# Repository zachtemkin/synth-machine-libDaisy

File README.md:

# synthMachine

## Author

<!-- Insert Your Name Here -->

## Description

<!-- Describe your example here -->

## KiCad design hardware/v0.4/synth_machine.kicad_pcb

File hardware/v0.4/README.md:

# synthMachine carrier board v0.4

Second revision of the carrier. v0.3 in `../v0.3/` is the board that was
fabricated in September 2026; v0.4 applies everything in `../NEXT_REVISION.md`
and adds onboard battery power. It is a new outline: 160 x 74 mm landscape
instead of 100 x 100, with all 19 key headers in one row along the bottom
edge in panel order. The USB-C, the Seed's own USB and the headphone jack
still share the top edge.

| Change | Parts | Why |
|---|---|---|
| One row of key headers | K1..K19 along the bottom at 7 mm pitch, diode above each, name below | Every button lead is the same length and points the same way. The headers are rotated so the row is 132 mm wide and the corners stay free for mounting holes. |
| Battery power | J17 JST-PH cell, U5 BQ24074 charger with power path, U6 TPS61023 5 V boost, J16 power-switch header, JP2 always-on jumper | Runs from a single LiPo, charges from the USB-C, and runs from USB while charging. See the power section below. |
| Plug detect reaches 3V3 | Q1 is a 2N7002 MOSFET | The v0.3 BJT clamped HP_DET at 0.8 V so D13 never saw a plug. No jumper, no `HP_DET=adc`. |
| Firmware mute on its own transistor | Q2 2N7002, R6 gate, R15 pull-up; MUTE on D0 | Muted at reset, in DFU and after a crash; firmware drives D0 low to run. Wired-OR with Q1. |
| I2C for encoders | J15 STEMMA QT (top-entry) on I2C1 (D11 SCL, D12 SDA) at the top right; R16/R17 pull-ups DNP | For the seesaw rotary-encoder breakouts; the cable leaves upward toward the panel. |
| Display header | J9: GND, 3V3, 5V, SCK (A7), MOSI (A3), NSS (A8), D/C (D26), RST (D27) | Hardware SPI1 for an OLED or a Sharp memory LCD. |
| Encoders instead of bank pots | J11..J14 removed; only J10 (volume) remains | The four bank controls are seesaw rotary encoders on J15. Their old ADC pins go to the expansion header. |
| USB ESD, SMD fuse | U4 USBLC6-2SC6, F1 1812 PTC on the USB input | Data lines were unprotected; the radial fuse collided with the Seed. |
| USB-C receptacle | J1 is the HRO TYPE-C-31-M-12 (LCSC C165948) | Same land pattern and body depth as v0.3's GCT USB4105, which went out of stock. A JLCPCB basic part. |
| Peripheral 3.3 V rail | U7 AP7361C-33 (SOT-223, 1 A) from +5V, C27/C28 | Feeds the encoders, the display and the expansion header's 3V3 pin, so the Seed's regulator carries only the Seed, the headphone amp and pull-ups. |
| Assembly-ready BOM | every part has an MPN or LCSC number | `fab.sh` writes `pcbway_bom.csv` / `pcbway_cpl.csv`. |

Only the volume pot header remains (A0). The four bank controls are I2C
rotary encoders on J15, chained over STEMMA QT. The firmware profile
`HW=carrier4` reads A0 only and leaves the bank inputs alone until the
encoder support exists.

## Power

```
USB-C J1 -> F1 2.5 A PTC -> VUSB -> U5 BQ24074 IN
                                    U5 BAT  <-> J17 cell (+ C22)
                                    U5 OUT   -> VSYS (4.4 V on USB, else the cell)
VSYS -> L1 1 uH / U6 TPS61023 -> +5V (5.1 V) -> Seed VIN, speaker amp, J8/J9 5V pins
                                       +5V -> U7 AP7361C-33 -> 3V3P -> J15 encoders, J9 display, J8 3V3
```

- **Charger.** EN2 high and EN1 low select the resistor-programmed input
  limit: R19 1.1k gives 1.5 A, and the charger's input-voltage loop backs off
  automatically on a weak USB port. R18 1.8k sets 0.5 A fast charge, which is
  0.25 C for a 2000 mAh cell and keeps the linear charger under 0.7 W. TMR and
  ITERM are left open for the default 30 min / 5 h safety timers and 10 %
  termination. CE is tied low, TS has the 10k that the part needs when there
  is no pack thermistor. The system runs from OUT while the cell charges, and
  the cell supplements USB on peaks.
- **Boost.** The TPS61023 makes 5.1 V from VSYS (750k/100k on a 0.6 V
  reference). It carries the whole load on USB as well as on battery, which is
  fine: from the charger's 4.4 V it is barely working. From a 3.3 V cell it
  delivers about 1.5 A continuous with the 470 uF C1 covering the amp's
  peaks. Inductor per TI's table (Coilcraft XEL4030-102ME); XGL4030-102MEC is
  the LCSC-stocked equivalent.
- **Switch.** J16 takes a panel SPST. Closed, it pulls the boost's EN up to
  VSYS through R28; open, R27 holds it low and everything downstream of the
  boost is off, while the charger keeps charging. The EN pin draws nothing,
  so any small switch works. J16 sits on the left edge at mid-height with JP2
  beside it to bridge the switch on a bench board; the two enable lines run
  across the board to the boost, which is fine for a pull-up-and-pin signal.
- **Firmware signals.** A10 reads VBAT/2 (R23/R24, 0 to 2.1 V). A5 reads
  ~CHG (low = charging) and A11 reads ~PGOOD (low = USB present), both
  open-drain with 100k pull-ups. Nothing in the firmware uses them yet.
- **Cell.** Single-cell LiPo on J17, pin 1 = +. Use a protected cell (the
  Adafruit and SparkFun packs are); there is no protection on the board.
  2000 mAh or more suits the speakers, which can pull over 1 A at volume.
- **Note.** The Seed's own USB port powers only the Seed; it cannot charge
  the cell or run the amp. That was already true on v0.3.

## Regenerate, route, fab

Same pipeline as v0.3, run from this directory:

```bash
KICAD_PY=/Applications/KiCad/KiCad.app/Contents/Frameworks/Python.framework/Versions/Current/bin/python3
$KICAD_PY hardware/v0.4/gen_kicad.py                       # schematic + placed PCB
$KICAD_PY hardware/v0.4/route.py --java <java25> --jar freerouting-2.4.1.jar
$KICAD_PY hardware/v0.4/route.py --pours-only              # rebuild just the GND pours
sh hardware/v0.4/fab.sh                                    # Gerbers, BOMs, CPLs, test print
```

Freerouting 2.4.1 needs Java 25. Neither is installed system-wide on the
Mac; a portable Temurin JRE from adoptium.net and the jar from the Freerouting
GitHub releases page were used, and both can live anywhere. `PREROUTES` in
the generator carries the audio paths, the MAX98306 fan-out and short stubs
off the boost converter's 0.5 mm pitch pins, which the autorouter cannot reach
with power-width tracks on its own.

## Pin map (what the firmware profile `HW=carrier4` expects)

| Seed pin | Use |
|---|---|
| D0 | MUTE: high = speakers muted (default via R15), low = run |
| D1..D3 | matrix rows |
| D4..D9 | matrix columns |
| D10 | C4 key |
| D11, D12 | I2C1 SCL, SDA (STEMMA QT) |
| D13 | HP_DET, high = headphones plugged in |
| D14 | HP_MUTE, headphone amp ~MUTE, low = muted |
| A0 | volume pot |
| A1, A2, A4, A9 | spare, on J8 (the old bank pot inputs) |
| A3, A7, A8 | SPI1 MOSI, SCK, NSS (display) |
| A5 | ~CHG from the charger, low = charging |
| A6 | spare, on J8 (seesaw INT candidate) |
| A10 | battery voltage / 2 |
| A11 | ~PGOOD from the charger, low = USB present |
| D26, D27 | display D/C, RST |
| D29, D30 | USB-C data (MIDI) |

## Headers

| Ref | What | Pins |
|---|---|---|
| K1..K19 | keys, JST-XH 2-pin, bottom row in panel order | row / diode (any way round) |
| J10 | volume pot, JST-XH 3-pin, left edge below the USB-C | 3V3A, wiper, GND |
| J5, J6 | speakers, JST-PH | + / - |
| J17 | battery, JST-PH | 1 = +, 2 = GND |
| J16 | power switch, JST-XH 2-pin, left edge mid-height (JP2 beside it bridges it) | either way round |
| J15 | STEMMA QT, top-entry, top right | GND, 3V3P, SDA, SCL |
| J9 | display | GND, 3V3P, 5V, SCK, MOSI, NSS, D/C, RST |
| J8 | expansion | HP_MUTE, A1, A2, A4, A6, A9, HP_DET, MUTE, VSYS, 3V3P, 5V, GND |

## Ordering with assembly (PCBWay)

`fab.sh` writes `fab/pcbway_bom.csv` with an item per line: designators,
quantity, manufacturer part number, LCSC number, value, package and whether it
is SMD or through-hole. `fab/pcbway_cpl.csv` has both sides. Upload the
Gerber zip, the BOM and the CPL; on the quote, tick at least J1 (USB-C), the
19 K headers, J10, J5/J6, J16, J17 and J15 for placement. The Seed
sockets, C1 and the jack can go in the same job or be hand-fitted.

## Ordering with assembly (JLCPCB)

`fab/jlcpcb_bom.csv` and `fab/jlcpcb_cpl.csv` carry every part with an LCSC
number, which is all of the SMD parts and the JST connectors: the 19 key
headers, the volume and switch headers (JST XH originals, C158012 /
C144394) and the speaker and battery sockets (JST PH, C131337). Choose
**standard** assembly, not economic: economic is SMD-only and drops the
through-hole connectors. Still hand-fitted afterwards: the two Seed sockets,
the two expansion/display sockets, the headphone jack and C1, which are on
the Digi-Key list. The DNP pull-ups are excluded automatically.

## Design review notes (v0.4 quality pass)

Things checked after the layout settled, and what was changed or accepted:

- **Current paths.** Every net that carries real current was audited for
  width: VBUS/VUSB/VBAT/VSYS 0.4 mm, +5V and the filtered speaker lines
  0.6 mm, with 0.5 mm-drill vias. The only narrow copper left is the
  unavoidable necks onto fine-pitch pads: 0.3 mm for less than 1 mm at the
  boost's VIN/SW/VOUT/GND pins (0.35 mm pads, 0.5 mm pitch) and 0.2 mm for
  about 1 mm at the amp's PVDD and speaker pins (0.4 mm pitch). The amp's
  two PVDD pins are joined right off the pads into one 0.5 mm feed. The
  boost's input and output capacitors sit at its pins with 0.6 mm copper.
- **Power switch really switches off.** The TPS61023 has true input-to-output
  disconnect in shutdown, so with EN low nothing reaches the Seed's VIN.
- **Bulk capacitor on the boost.** The 470 uF electrolytic on +5V is inside
  the TPS61023's stated 4 to 1000 uF effective output range.
- **Boost thermals.** SOT-563 is about 120 to 140 K/W. At 1 A out from a
  3.3 V cell the part dissipates about 0.5 W, so it runs warm (60 K rise)
  but within limits; the amp's 2 A peaks are brief. Keep the ground pour
  under it. If a future revision needs more headroom, the TPS61088 in a
  QFN is the drop-in class.
- **Seed 3V3 budget.** Solved with a separate rail: the Seed's regulator
  feeds only the Seed, the headphone amp and the pull-ups (tens of
  milliamps). The encoders, display and expansion header run from U7, a
  1 A SOT-223 LDO on the +5V rail (3V3P). At 300 mA it dissipates about
  0.55 W, a 30 K rise on its ground tab and pour. On battery that rail is
  boost-then-LDO, roughly 60 % efficient, about 20 mA of extra cell current
  at typical loads. The headphone amp stays on the Seed's quieter rail.
- **USB-C current.** The CC pull-downs advertise a sink but the firmware does
  not read the source's advertisement, so the charger's 1.5 A input limit
  applies to any port; the charger's VIN-DPM loop throttles rather than
  crashes a 500 mA port. A CC ADC read would let firmware lower ILIM later.
- **Battery divider on the ADC.** 100k/100k is a 50k source impedance, high
  for the STM32 ADC's sampling time; the 100 nF across the bottom resistor
  is what makes the reading settle. Do not drop it.
- **Reverse cell.** No reverse-polarity protection on J17 by design (a diode
  would cost the charger its regulation). The polarity check below is the
  protection.
- **Quiescent when off.** Charger from the cell, boost leakage and the sense
  divider add up to about 25 uA, years on any usable cell.

## Check before ordering

1. **J17 polarity** against the cell you will use: pin 1 is + here, and the
   silkscreen says so. A reversed cell destroys the charger.
2. **J15 pin 1** (GND) is the pad nearest the board's right edge; check it
   against the cable's black wire before plugging in an encoder board.
3. **Q1/Q2 pinout:** KiCad's `Q_NMOS_GSD` is gate 1, source 2, drain 3, the
   2N7002's SOT-23 order. Check the LCSC part's datasheet agrees.
4. **U5 thermal pad** has vias to the ground pour; make sure the assembler's
   stencil does not flood it.
5. **Enclosure:** the outline changed. The top edge still carries all three
   ports at the same spacing from the left edge as v0.3, but the board is
   60 mm wider and 26 mm shorter, and the mounting holes moved. The headphone
   jack's nose now stands 1.5 mm proud of the edge instead of flush.
6. **F1 and L1 look unpopulated in the render** only because this KiCad
   install has no 3D models for the 1812 fuse and the XxL4030 inductor
   footprints. Both are in the BOM and the placement file.

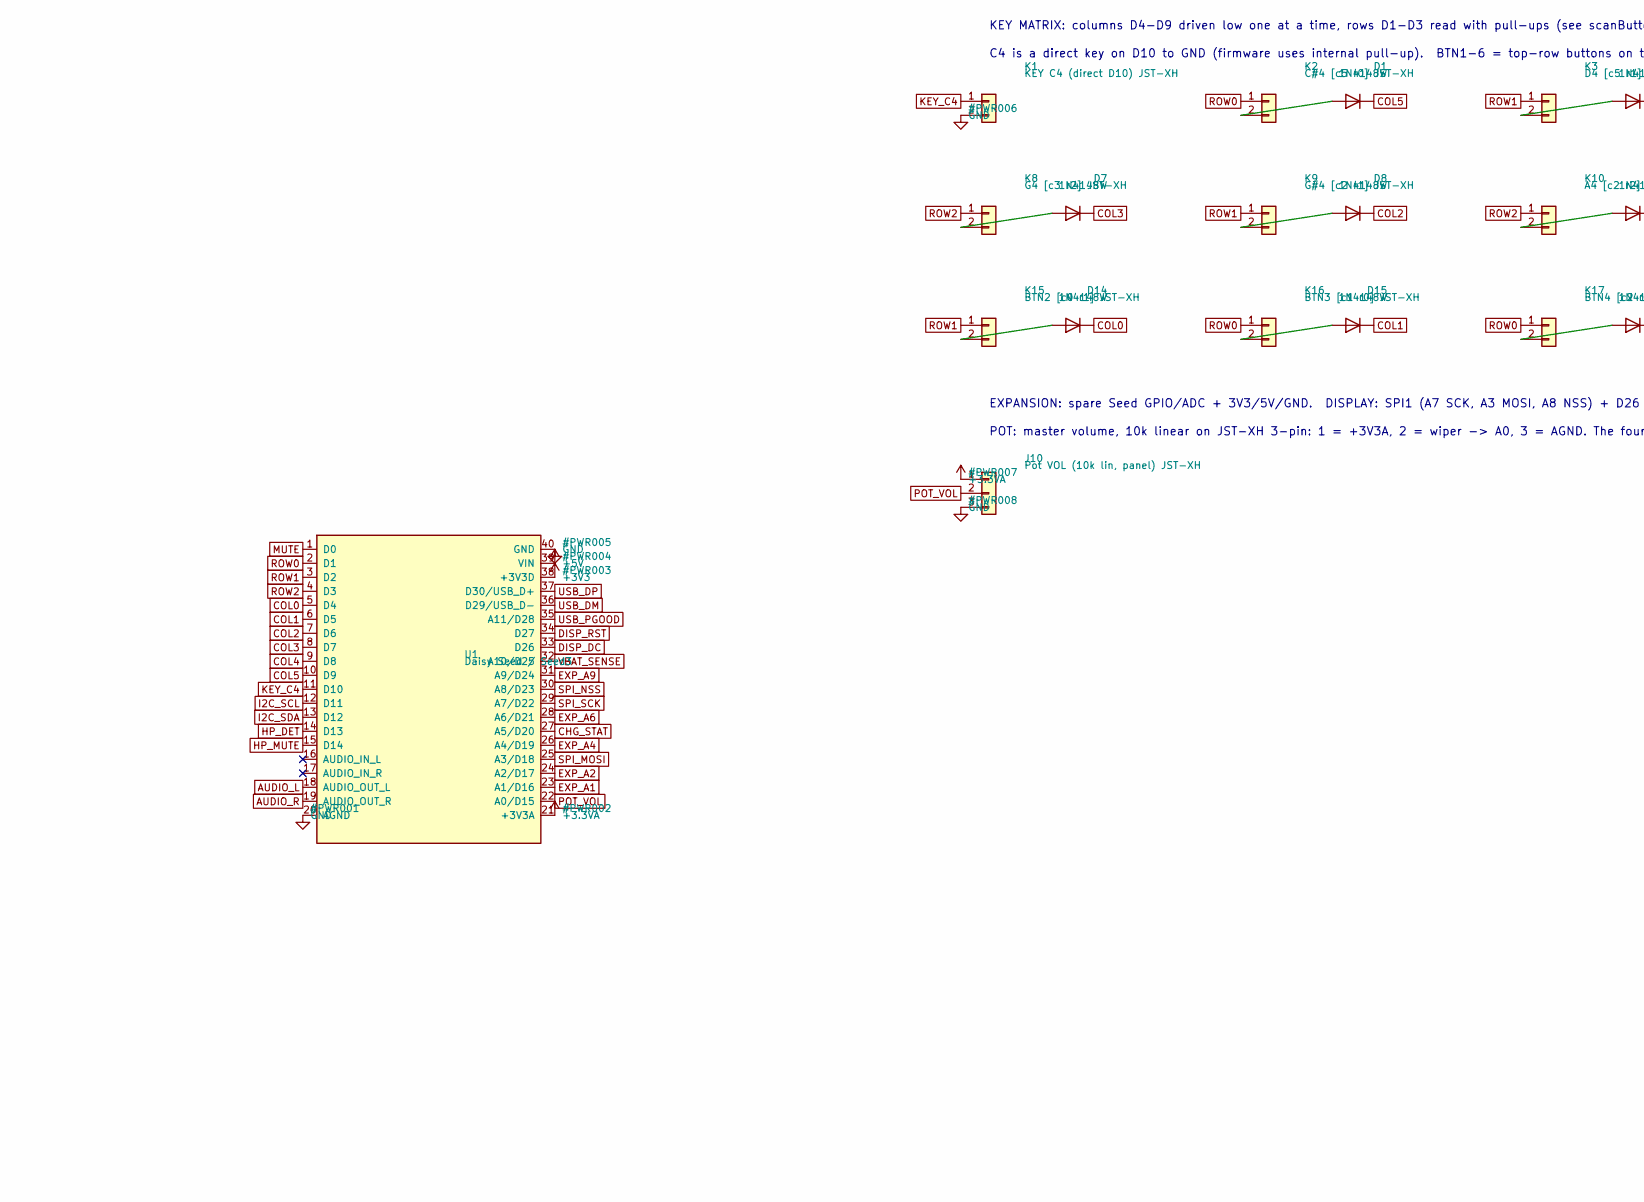
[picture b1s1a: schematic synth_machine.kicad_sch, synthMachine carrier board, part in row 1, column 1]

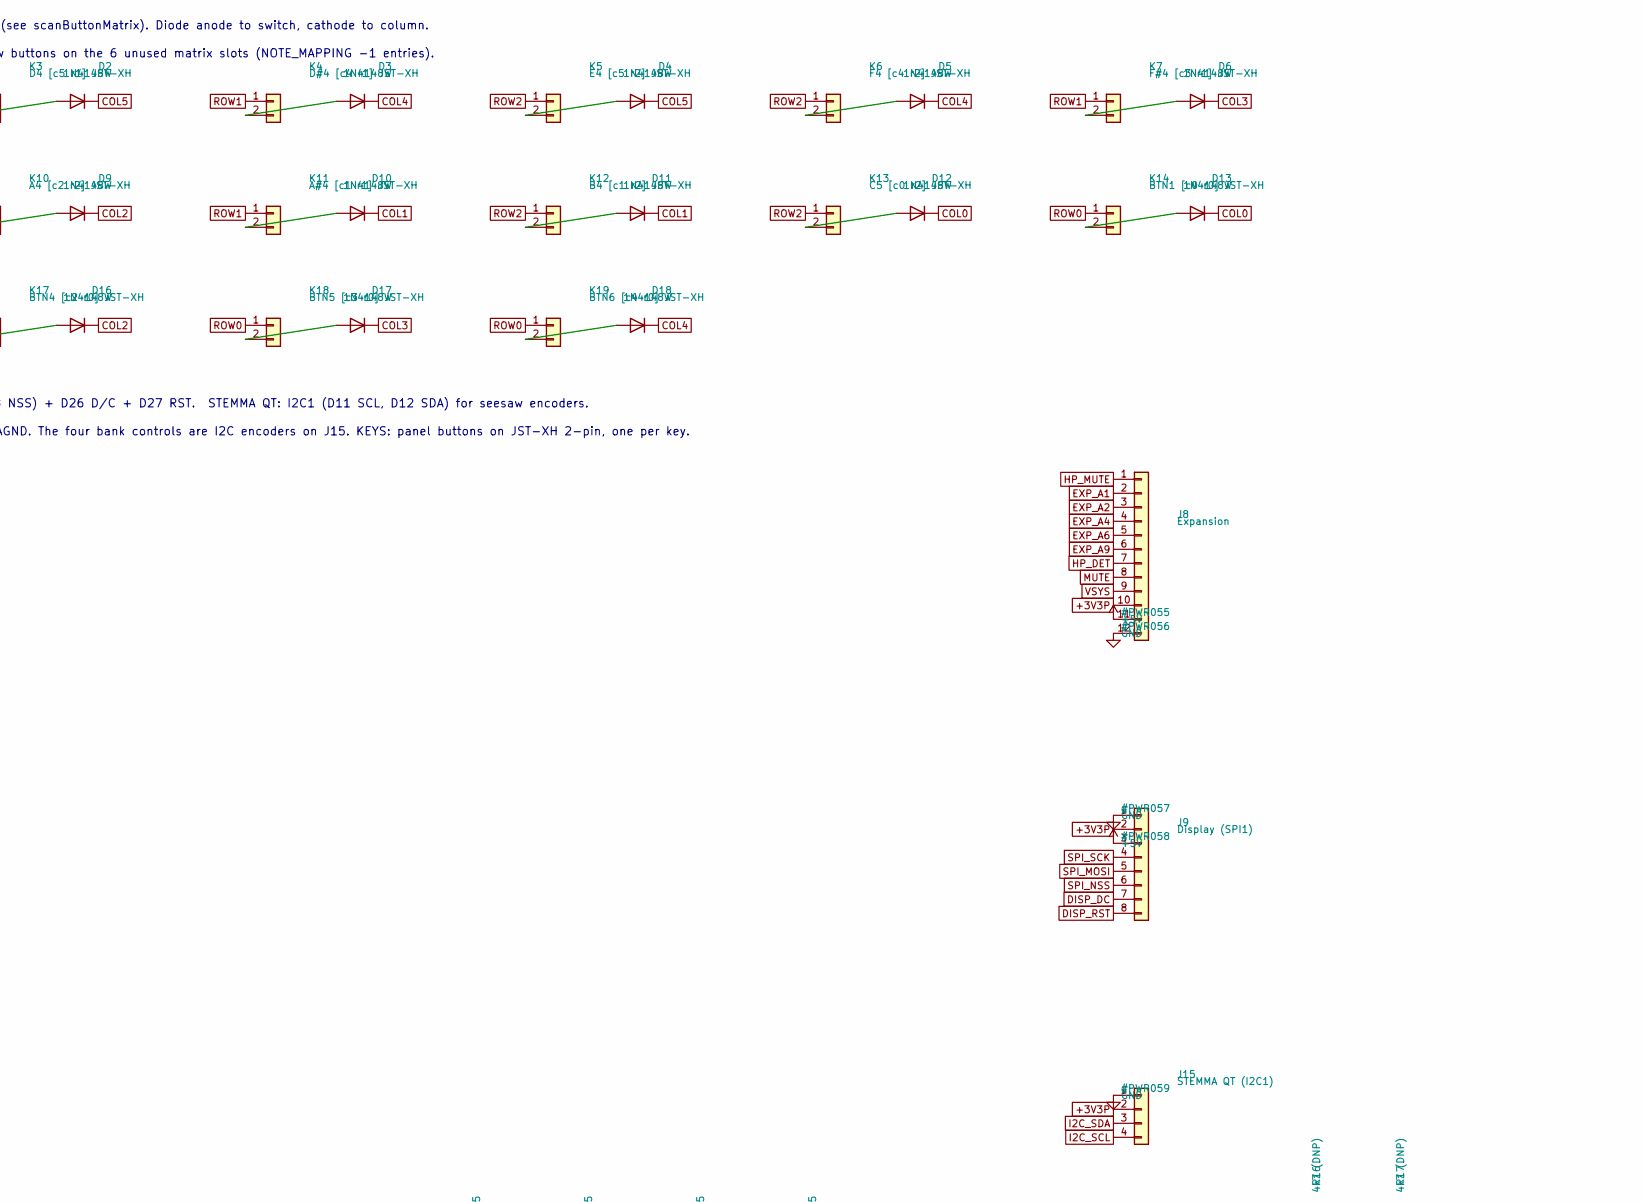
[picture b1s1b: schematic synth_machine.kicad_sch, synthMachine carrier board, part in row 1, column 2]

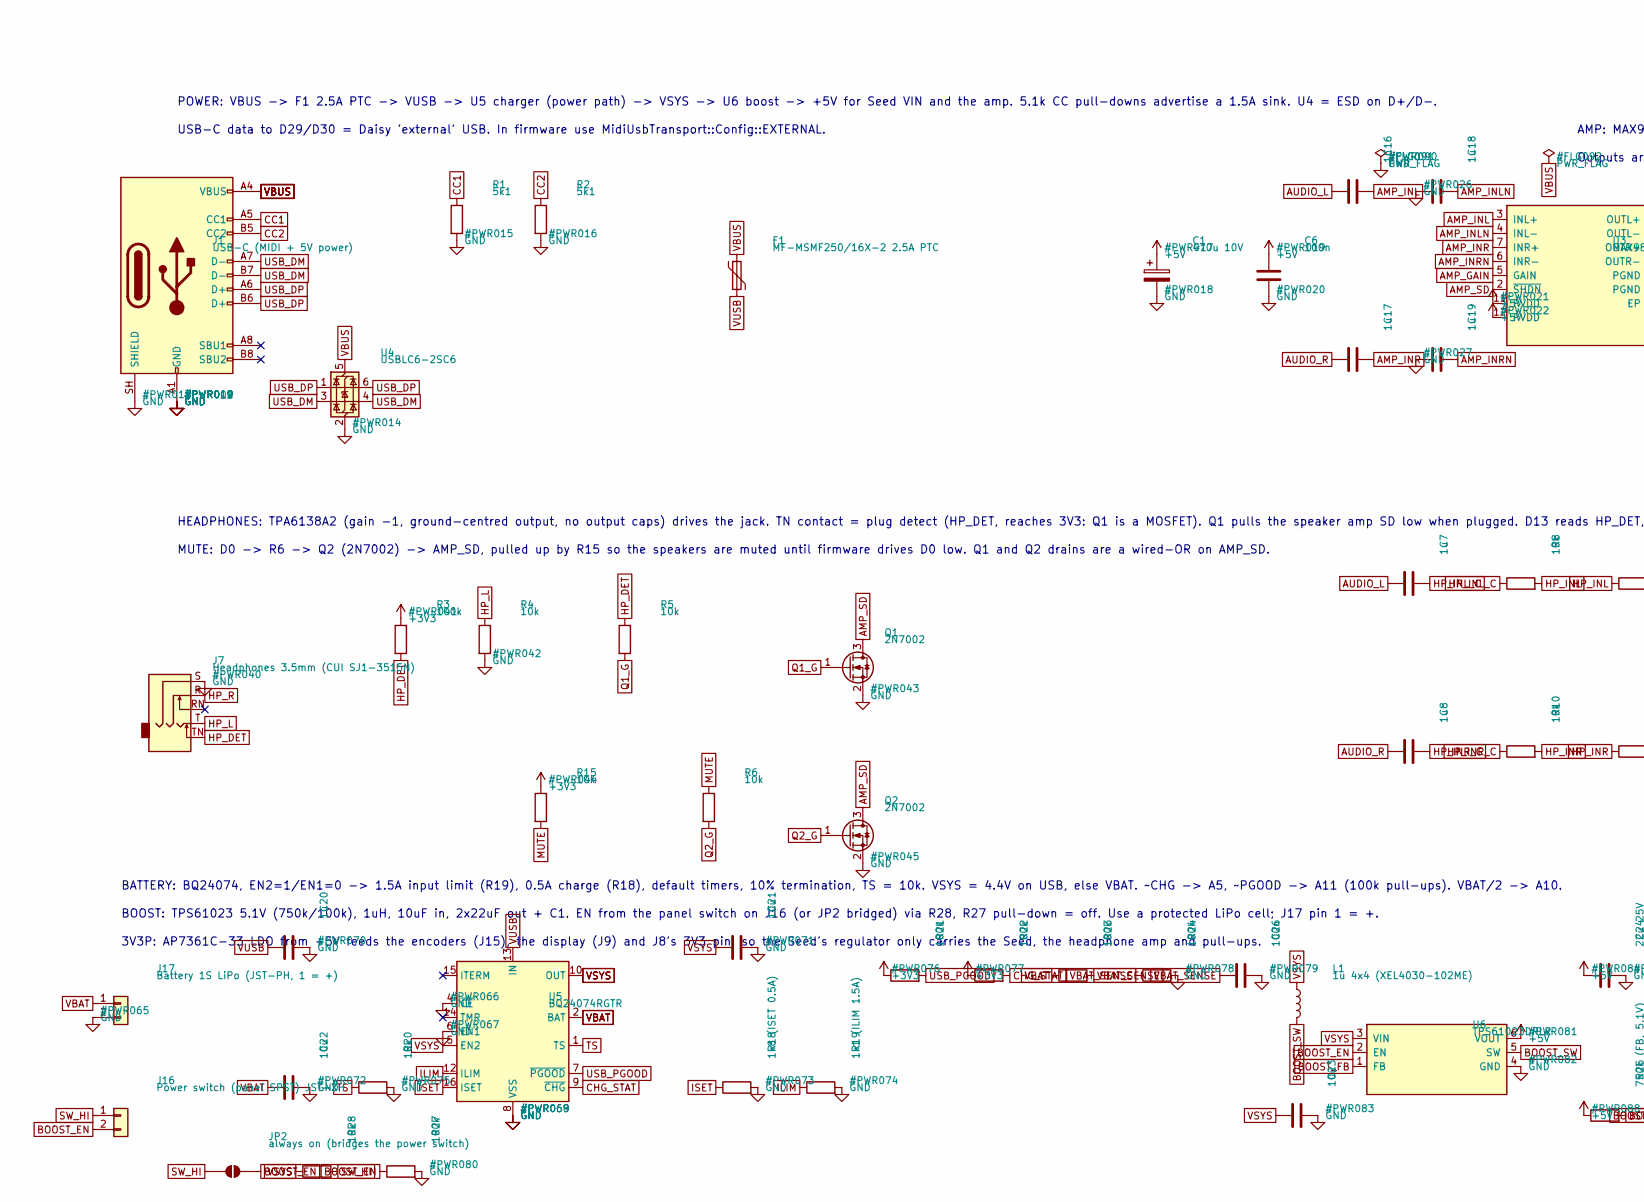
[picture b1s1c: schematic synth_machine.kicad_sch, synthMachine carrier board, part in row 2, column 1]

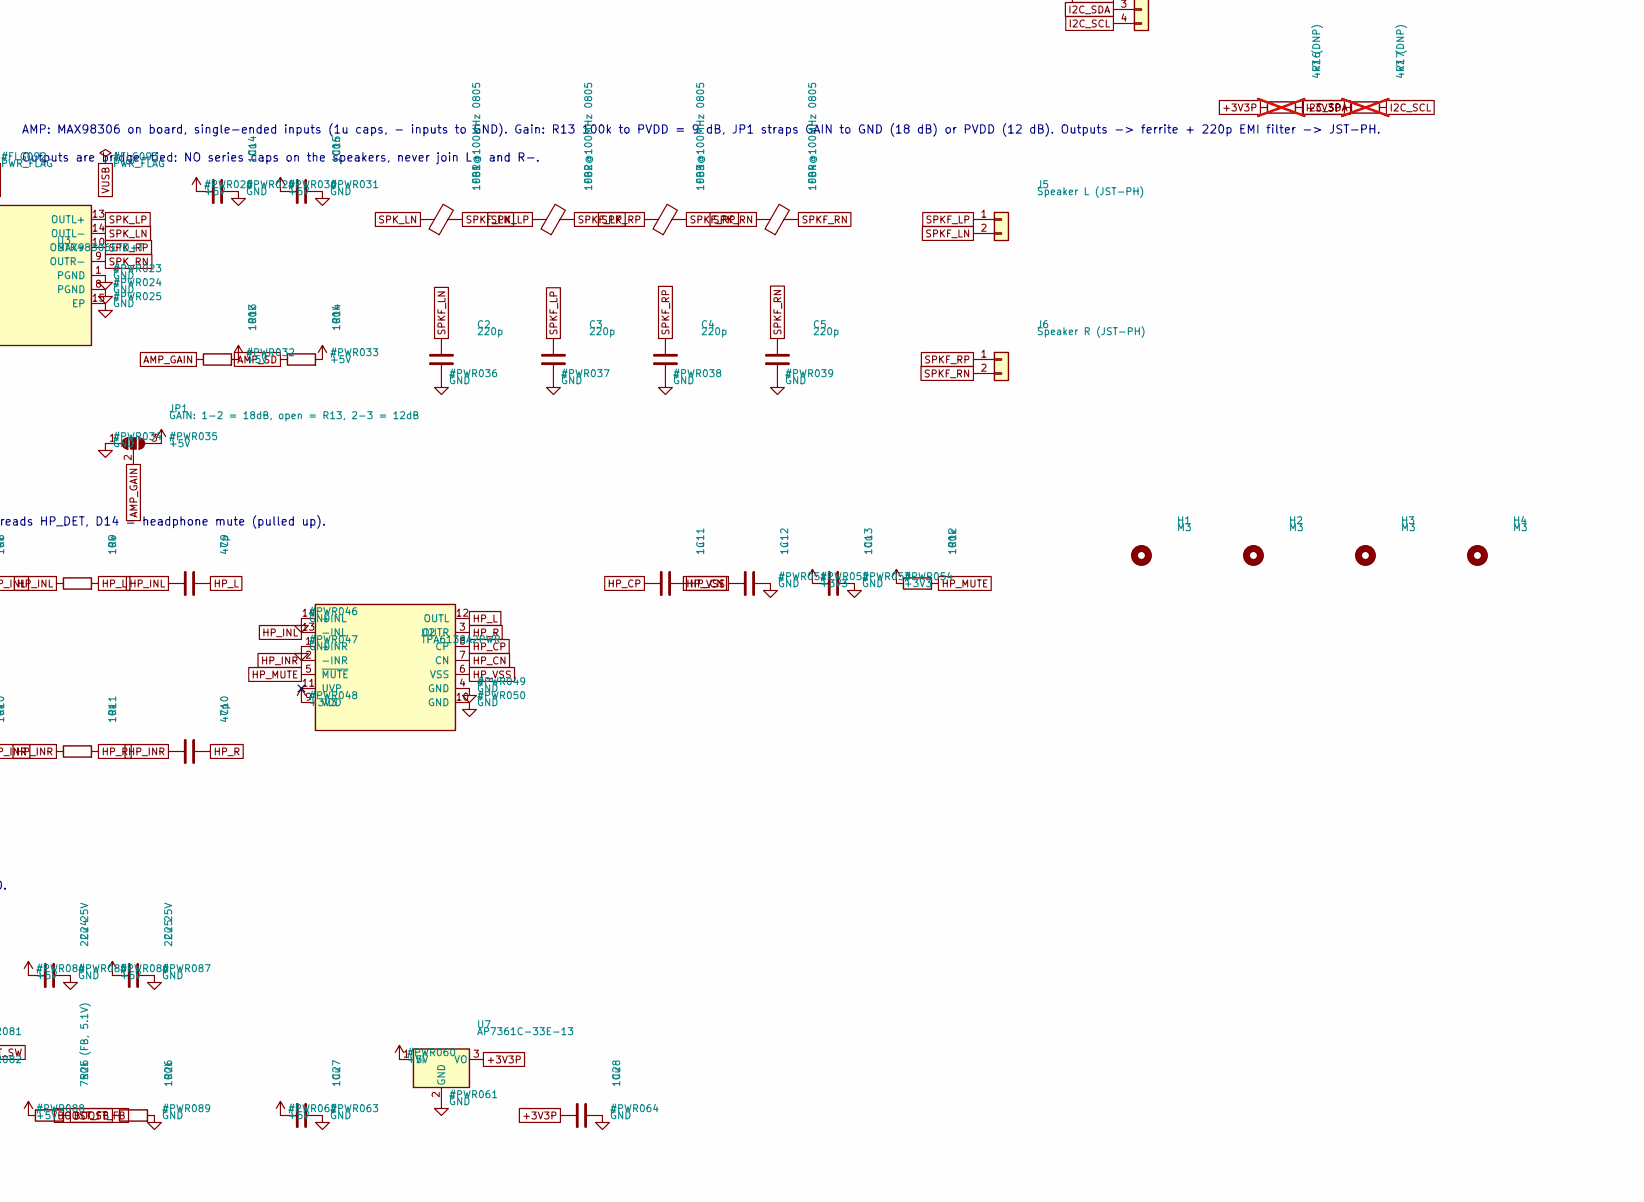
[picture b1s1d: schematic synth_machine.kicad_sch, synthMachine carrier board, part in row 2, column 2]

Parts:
C1: 470u 10V; CP_Radial_D8.0mm_P3.50mm; MPN EEU-FR1A471
C2, C3, C4, C5: 220p; C_0805_2012Metric; LCSC C53172
C6, C15, C26: 100n; C_0805_2012Metric; LCSC C49678
C7, C8, C11, C12, C16, C17, C18, C19, C20: 1u; C_0805_2012Metric; LCSC C28323
C9, C10: 47p; C_0805_2012Metric; LCSC C14857
C13, C14, C21, C22, C23, C27, C28: 10u; C_0805_2012Metric; LCSC C15850
C24, C25: 22u 25V; C_1210_3225Metric; MPN CL32A226KAJNNNE; LCSC C52306
D1, D2, D3, D4, D5, D6, D7, D8, D9, D10, D11, D12, D13, D14, D15, D16, D17, D18: 1N4148W; D_SOD-123; LCSC C81598
F1: MF-MSMF250/16X-2 2.5A PTC; Fuse_1812_4532Metric; MPN MF-MSMF250/16X-2; LCSC C210838
FB1, FB2, FB3, FB4: 100R@100MHz 0805; L_0805_2012Metric; LCSC C1015
H1, H2, H3, H4: M3; MountingHole_3.2mm_M3
J1: USB-C (MIDI + 5V power); USB_C_Receptacle_HRO_TYPE-C-31-M-12; MPN TYPE-C-31-M-12; LCSC C165948
J5: Speaker L (JST-PH); JST_PH_B2B-PH-K_1x02_P2.00mm_Vertical; MPN B2B-PH-K-S(LF)(SN); LCSC C131337
J6: Speaker R (JST-PH); JST_PH_B2B-PH-K_1x02_P2.00mm_Vertical; MPN B2B-PH-K-S(LF)(SN); LCSC C131337
J7: Headphones 3.5mm (CUI SJ1-3515N); Jack_3.5mm_CUI_SJ1-3515N_Horizontal; MPN SJ1-3515N
J8: Expansion; PinHeader_1x12_P2.54mm_Vertical; MPN PPTC121LFBN-RC
J9: Display (SPI1); PinHeader_1x08_P2.54mm_Vertical; MPN PPTC081LFBN-RC
J10: Pot VOL (10k lin, panel) JST-XH; JST_XH_B3B-XH-A_1x03_P2.50mm_Vertical; MPN B3B-XH-A(LF)(SN); LCSC C144394
J15: STEMMA QT (I2C1); JST_SH_BM04B-SRSS-TB_1x04-1MP_P1.00mm_Vertical; MPN BM04B-SRSS-TB(LF)(SN); LCSC C160390
J16: Power switch (panel SPST) JST-XH; JST_XH_B2B-XH-A_1x02_P2.50mm_Vertical; MPN B2B-XH-A(LF)(SN); LCSC C158012
J17: Battery 1S LiPo (JST-PH, 1 = +); JST_PH_B2B-PH-K_1x02_P2.00mm_Vertical; MPN B2B-PH-K-S(LF)(SN); LCSC C131337
JP1: GAIN: 1-2 = 18dB, open = R13, 2-3 = 12dB; SolderJumper-3_P1.3mm_Open_RoundedPad1.0x1.5mm
JP2: always on (bridges the power switch); SolderJumper-2_P1.3mm_Open_RoundedPad1.0x1.5mm
K1: KEY C4 (direct D10) JST-XH; JST_XH_B2B-XH-A_1x02_P2.50mm_Vertical; MPN B2B-XH-A(LF)(SN); LCSC C158012
K2: C#4 [c5 r0] JST-XH; JST_XH_B2B-XH-A_1x02_P2.50mm_Vertical; MPN B2B-XH-A(LF)(SN); LCSC C158012
K3: D4 [c5 r1] JST-XH; JST_XH_B2B-XH-A_1x02_P2.50mm_Vertical; MPN B2B-XH-A(LF)(SN); LCSC C158012
K4: D#4 [c4 r1] JST-XH; JST_XH_B2B-XH-A_1x02_P2.50mm_Vertical; MPN B2B-XH-A(LF)(SN); LCSC C158012
K5: E4 [c5 r2] JST-XH; JST_XH_B2B-XH-A_1x02_P2.50mm_Vertical; MPN B2B-XH-A(LF)(SN); LCSC C158012
K6: F4 [c4 r2] JST-XH; JST_XH_B2B-XH-A_1x02_P2.50mm_Vertical; MPN B2B-XH-A(LF)(SN); LCSC C158012
K7: F#4 [c3 r1] JST-XH; JST_XH_B2B-XH-A_1x02_P2.50mm_Vertical; MPN B2B-XH-A(LF)(SN); LCSC C158012
K8: G4 [c3 r2] JST-XH; JST_XH_B2B-XH-A_1x02_P2.50mm_Vertical; MPN B2B-XH-A(LF)(SN); LCSC C158012
K9: G#4 [c2 r1] JST-XH; JST_XH_B2B-XH-A_1x02_P2.50mm_Vertical; MPN B2B-XH-A(LF)(SN); LCSC C158012
K10: A4 [c2 r2] JST-XH; JST_XH_B2B-XH-A_1x02_P2.50mm_Vertical; MPN B2B-XH-A(LF)(SN); LCSC C158012
K11: A#4 [c1 r1] JST-XH; JST_XH_B2B-XH-A_1x02_P2.50mm_Vertical; MPN B2B-XH-A(LF)(SN); LCSC C158012
K12: B4 [c1 r2] JST-XH; JST_XH_B2B-XH-A_1x02_P2.50mm_Vertical; MPN B2B-XH-A(LF)(SN); LCSC C158012
K13: C5 [c0 r2] JST-XH; JST_XH_B2B-XH-A_1x02_P2.50mm_Vertical; MPN B2B-XH-A(LF)(SN); LCSC C158012
K14: BTN1 [c0 r0] JST-XH; JST_XH_B2B-XH-A_1x02_P2.50mm_Vertical; MPN B2B-XH-A(LF)(SN); LCSC C158012
K15: BTN2 [c0 r1] JST-XH; JST_XH_B2B-XH-A_1x02_P2.50mm_Vertical; MPN B2B-XH-A(LF)(SN); LCSC C158012
K16: BTN3 [c1 r0] JST-XH; JST_XH_B2B-XH-A_1x02_P2.50mm_Vertical; MPN B2B-XH-A(LF)(SN); LCSC C158012
K17: BTN4 [c2 r0] JST-XH; JST_XH_B2B-XH-A_1x02_P2.50mm_Vertical; MPN B2B-XH-A(LF)(SN); LCSC C158012
K18: BTN5 [c3 r0] JST-XH; JST_XH_B2B-XH-A_1x02_P2.50mm_Vertical; MPN B2B-XH-A(LF)(SN); LCSC C158012
K19: BTN6 [c4 r0] JST-XH; JST_XH_B2B-XH-A_1x02_P2.50mm_Vertical; MPN B2B-XH-A(LF)(SN); LCSC C158012
L1: 1u 4x4 (XEL4030-102ME); L_Coilcraft_XxL4030; MPN XEL4030-102MEC
Q1, Q2: 2N7002; SOT-23; MPN 2N7002; LCSC C8545
R1, R2: 5k1; R_0805_2012Metric; LCSC C27834
R3, R12, R13, R14, R21, R22, R23, R24, R26, R27: 100k; R_0805_2012Metric; LCSC C149504
R4, R5, R6, R8, R9, R10, R11, R15, R20, R28: 10k; R_0805_2012Metric; LCSC C17414
R16, R17: 4k7 (DNP); R_0805_2012Metric; not fitted
R18: 1k8 (ISET 0.5A); R_0805_2012Metric; MPN 0805 1% 1.8k
R19: 1k1 (ILIM 1.5A); R_0805_2012Metric; MPN 0805 1% 1.1k
R25: 750k (FB, 5.1V); R_0805_2012Metric; MPN 0805 1% 750k
U1: Daisy Seed / Seed3; DaisySeed_2x20; MPN PPTC201LFBN-RC x2 (sockets; the Seed it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
U2: TPA6138A2PWR; TSSOP-14_4.4x5mm_P0.65mm; MPN TPA6138A2PWR; LCSC C183097
U3: MAX98306ETD+T; TDFN-14-1EP_3x3mm_P0.4mm_EP1.78x2.35mm_ThermalVias; MPN MAX98306ETD+T; LCSC C124549
U4: USBLC6-2SC6; SOT-23-6; MPN USBLC6-2SC6; LCSC C7519
U5: BQ24074RGTR; VQFN-16-1EP_3x3mm_P0.5mm_EP1.6x1.6mm_ThermalVias; MPN BQ24074RGTR; LCSC C54313
U6: TPS61023DRLR; SOT-563; MPN TPS61023DRLR; LCSC C919459
U7: AP7361C-33E-13; SOT-223-3_TabPin2; MPN AP7361C-33E-13; LCSC C500795

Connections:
+3.3VA: J10.1, U1.21 (+3V3A)
+3V3: C13.1, R3.1, R12.1, R15.1, R21.1, R22.1, U1.38 (+3V3D), U2.9 (VDD)
+3V3P: C28.1, J8.10, J9.2, J15.2, R16.1, R17.1, U7.3 (VO)
+5V: C1.1, C6.1, C14.1, C15.1, C24.1, C25.1, C27.1, J8.11, J9.3, JP1.3 (B), R13.2, R14.2, R25.1, U1.39 (VIN), U3.11 (PVDD), U3.12 (PVDD), U6.6 (VOUT), U7.1 (VI)
AMP_GAIN: JP1.2 (C), R13.1, U3.5 (GAIN)
AMP_INL: C16.2, U3.3 (INL+)
AMP_INLN: C18.2, U3.4 (INL-)
AMP_INR: C17.2, U3.7 (INR+)
AMP_INRN: C19.2, U3.6 (INR-)
AMP_SD: Q1.3 (D), Q2.3 (D), R14.1, U3.2 (~SHDN)
AUDIO_L: C7.1, C16.1, U1.18 (AUDIO_OUT_L)
AUDIO_R: C8.1, C17.1, U1.19 (AUDIO_OUT_R)
BOOST_EN: J16.2, JP2.2 (B), R27.1, U6.2 (EN)
BOOST_FB: R25.2, R26.1, U6.1 (FB)
BOOST_SW: L1.2, U6.5 (SW)
CC1: J1.A5 (CC1), R1.1
CC2: J1.B5 (CC2), R2.1
CHG_STAT: R22.2, U1.27 (A5/D20), U5.9 (~CHG)
COL0: D12.1 (K), D13.1 (K), D14.1 (K), U1.5 (D4)
COL1: D10.1 (K), D11.1 (K), D15.1 (K), U1.6 (D5)
COL2: D8.1 (K), D9.1 (K), D16.1 (K), U1.7 (D6)
COL3: D6.1 (K), D7.1 (K), D17.1 (K), U1.8 (D7)
COL4: D3.1 (K), D5.1 (K), D18.1 (K), U1.9 (D8)
COL5: D1.1 (K), D2.1 (K), D4.1 (K), U1.10 (D9)
DISP_DC: J9.7, U1.33 (D26)
DISP_RST: J9.8, U1.34 (D27)
EXP_A1: J8.2, U1.23 (A1/D16)
EXP_A2: J8.3, U1.24 (A2/D17)
EXP_A4: J8.4, U1.26 (A4/D19)
EXP_A6: J8.5, U1.28 (A6/D21)
EXP_A9: J8.6, U1.31 (A9/D24)
GND: C1.2, C2.2, C3.2, C4.2, C5.2, C6.2, C12.2, C13.2, C14.2, C15.2, C18.1, C19.1, C20.2, C21.2, C22.2, C23.2, C24.2, C25.2, C26.2, C27.2, C28.2, J1.A1 (GND), J1.A12 (GND), J1.B1 (GND), J1.B12 (GND), J1.SH (SHIELD), J7.S, J8.12, J9.1, J10.3, J15.1, J17.2, JP1.1 (A), K1.2, Q1.2 (S), Q2.2 (S), R1.2, R2.2, R4.2, R18.2, R19.2, R20.2, R24.2, R26.2, R27.2, U1.20 (AGND), U1.40 (GND), U2.1 (+INR), U2.4 (GND), U2.10 (GND), U2.14 (+INL), U3.1 (PGND), U3.8 (PGND), U3.15 (EP), U4.2 (GND), U5.4 (~CE), U5.6 (EN1), U5.8 (VSS), U5.17 (VSS), U6.4 (GND), U7.2 (GND)
HP_CN: C11.2, U2.7 (CN)
HP_CP: C11.1, U2.8 (CP)
HP_DET: J7.TN, J8.7, R3.2, R5.1, U1.14 (D13)
HP_INL: C9.1, R8.2, R9.1, U2.13 (-INL)
HP_INL_C: C7.2, R8.1
HP_INR: C10.1, R10.2, R11.1, U2.2 (-INR)
HP_INR_C: C8.2, R10.1
HP_L: C9.2, J7.T, R4.1, R9.2, U2.12 (OUTL)
HP_MUTE: J8.1, R12.2, U1.15 (D14), U2.5 (~MUTE)
HP_R: C10.2, J7.R, R11.2, U2.3 (OUTR)
HP_VSS: C12.1, U2.6 (VSS)
I2C_SCL: J15.4, R17.2, U1.12 (D11)
I2C_SDA: J15.3, R16.2, U1.13 (D12)
ILIM: R19.1, U5.12 (ILIM)
ISET: R18.1, U5.16 (ISET)
KA4_D: D9.2 (A), K10.2
KAs4_D: D10.2 (A), K11.2
KB4_D: D11.2 (A), K12.2
KBTN1_D: D13.2 (A), K14.2
KBTN2_D: D14.2 (A), K15.2
KBTN3_D: D15.2 (A), K16.2
KBTN4_D: D16.2 (A), K17.2
KBTN5_D: D17.2 (A), K18.2
KBTN6_D: D18.2 (A), K19.2
KC5_D: D12.2 (A), K13.2
KCs4_D: D1.2 (A), K2.2
KD4_D: D2.2 (A), K3.2
KDs4_D: D3.2 (A), K4.2
KE4_D: D4.2 (A), K5.2
KEY_C4: K1.1, U1.11 (D10)
KF4_D: D5.2 (A), K6.2
KFs4_D: D6.2 (A), K7.2
KG4_D: D7.2 (A), K8.2
KGs4_D: D8.2 (A), K9.2
MUTE: J8.8, R6.1, R15.2, U1.1 (D0)
POT_VOL: J10.2, U1.22 (A0/D15)
Q1_G: Q1.1 (G), R5.2
Q2_G: Q2.1 (G), R6.2
ROW0: K2.1, K14.1, K16.1, K17.1, K18.1, K19.1, U1.2 (D1)
ROW1: K3.1, K4.1, K7.1, K9.1, K11.1, K15.1, U1.3 (D2)
ROW2: K5.1, K6.1, K8.1, K10.1, K12.1, K13.1, U1.4 (D3)
SPI_MOSI: J9.5, U1.25 (A3/D18)
SPI_NSS: J9.6, U1.30 (A8/D23)
SPI_SCK: J9.4, U1.29 (A7/D22)
SPKF_LN: C2.1, FB1.2, J5.2
SPKF_LP: C3.1, FB2.2, J5.1
SPKF_RN: C5.1, FB4.2, J6.2
SPKF_RP: C4.1, FB3.2, J6.1
SPK_LN: FB1.1, U3.14 (OUTL-)
SPK_LP: FB2.1, U3.13 (OUTL+)
SPK_RN: FB4.1, U3.9 (OUTR-)
SPK_RP: FB3.1, U3.10 (OUTR+)
SW_HI: J16.1, JP2.1 (A), R28.2
TS: R20.1, U5.1 (TS)
USB_DM: J1.A7 (D-), J1.B7 (D-), U1.36 (D29/USB_D-), U4.3 (I/O2), U4.4 (I/O2)
USB_DP: J1.A6 (D+), J1.B6 (D+), U1.37 (D30/USB_D+), U4.1 (I/O1), U4.6 (I/O1)
USB_PGOOD: R21.2, U1.35 (A11/D28), U5.7 (~PGOOD)
VBAT: C22.1, J17.1, R23.1, U5.2 (BAT), U5.3 (BAT)
VBAT_SENSE: C26.1, R23.2, R24.1, U1.32 (A10/D25)
VBUS: F1.1, J1.A4 (VBUS), J1.A9 (VBUS), J1.B4 (VBUS), J1.B9 (VBUS), U4.5 (VBUS)
VSYS: C21.1, C23.1, J8.9, L1.1, R28.1, U5.5 (EN2), U5.10 (OUT), U5.11 (OUT), U6.3 (VIN)
VUSB: C20.1, F1.2, U5.13 (IN)

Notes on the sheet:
KEY MATRIX: columns D4-D9 driven low one at a time, rows D1-D3 read with pull-ups (see scanButtonMatrix). Diode anode to switch, cathode to column.
C4 is a direct key on D10 to GND (firmware uses internal pull-up). BTN1-6 = top-row buttons on the 6 unused matrix slots (NOTE_MAPPING -1 entries).
POT: master volume, 10k linear on JST-XH 3-pin: 1 = +3V3A, 2 = wiper -> A0, 3 = AGND. The four bank controls are I2C encoders on J15. KEYS: panel buttons on JST-XH 2-pin, one per key.
POWER: VBUS -> F1 2.5A PTC -> VUSB -> U5 charger (power path) -> VSYS -> U6 boost -> +5V for Seed VIN and the amp. 5.1k CC pull-downs advertise a 1.5A sink. U4 = ESD on D+/D-.
USB-C data to D29/D30 = Daisy 'external' USB. In firmware use MidiUsbTransport::Config::EXTERNAL.
AMP: MAX98306 on board, single-ended inputs (1u caps, - inputs to GND). Gain: R13 100k to PVDD = 9 dB, JP1 straps GAIN to GND (18 dB) or PVDD (12 dB). Outputs -> ferrite + 220p EMI filter -> JST-PH.
Outputs are bridge-tied: NO series caps on the speakers, never join L- and R-.
HEADPHONES: TPA6138A2 (gain -1, ground-centred output, no output caps) drives the jack. TN contact = plug detect (HP_DET, reaches 3V3: Q1 is a MOSFET). Q1 pulls the speaker amp SD low when plugged. D13 reads HP_DET, D14 = headphone mute (pulled up).
MUTE: D0 -> R6 -> Q2 (2N7002) -> AMP_SD, pulled up by R15 so the speakers are muted until firmware drives D0 low. Q1 and Q2 drains are a wired-OR on AMP_SD.
BATTERY: BQ24074, EN2=1/EN1=0 -> 1.5A input limit (R19), 0.5A charge (R18), default timers, 10% termination, TS = 10k. VSYS = 4.4V on USB, else VBAT. ~CHG -> A5, ~PGOOD -> A11 (100k pull-ups). VBAT/2 -> A10.
BOOST: TPS61023 5.1V (750k/100k), 1uH, 10uF in, 2x22uF out + C1. EN from the panel switch on J16 (or JP2 bridged) via R28, R27 pull-down = off. Use a protected LiPo cell; J17 pin 1 = +.
3V3P: AP7361C-33 LDO from +5V feeds the encoders (J15), the display (J9) and J8's 3V3 pin, so the Seed's regulator only carries the Seed, the headphone amp and pull-ups.
EXPANSION: spare Seed GPIO/ADC + 3V3/5V/GND. DISPLAY: SPI1 (A7 SCK, A3 MOSI, A8 NSS) + D26 D/C + D27 RST. STEMMA QT: I2C1 (D11 SCL, D12 SDA) for seesaw encoders.

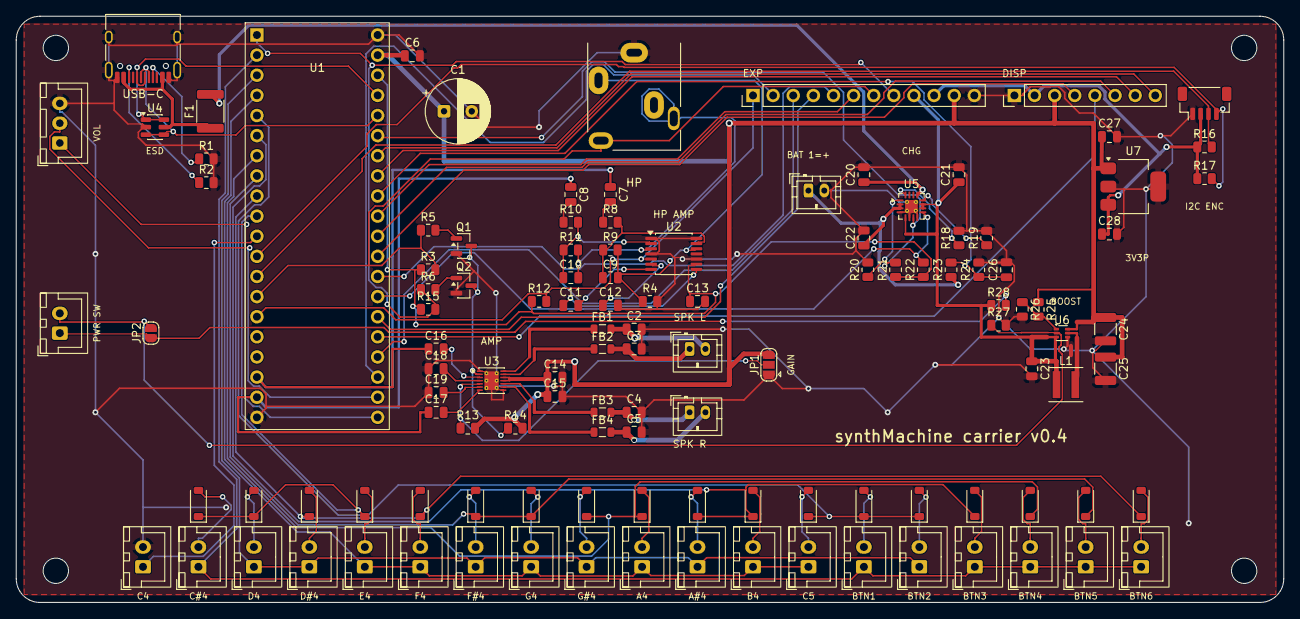
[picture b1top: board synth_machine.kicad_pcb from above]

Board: 2 copper layers, 160.0 x 74.0 mm, 123 parts (0 on the bottom side), 94 nets.

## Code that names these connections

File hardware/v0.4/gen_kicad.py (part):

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    22: ("A0/D15", "bidirectional", "POT_VOL"),
    23: ("A1/D16", "bidirectional", "EXP_A1"),
    24: ("A2/D17", "bidirectional", "EXP_A2"),
    25: ("A3/D18", "bidirectional", "SPI_MOSI"),    # SPI1 MOSI (PA7) for the display
    26: ("A4/D19", "bidirectional", "EXP_A4"),
    27: ("A5/D20", "bidirectional", "CHG_STAT"),     # ~CHG from the charger, low = charging
    28: ("A6/D21", "bidirectional", "EXP_A6"),
    29: ("A7/D22", "bidirectional", "SPI_SCK"),     # SPI1 SCK (PA5)
    30: ("A8/D23", "bidirectional", "SPI_NSS"),     # SPI1 NSS (PA4)
    31: ("A9/D24", "bidirectional", "EXP_A9"),
    32: ("A10/D25", "bidirectional", "VBAT_SENSE"),  # battery voltage / 2
    33: ("D26", "bidirectional", "DISP_DC"),
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        {"1": "SPKF_" + sig, "2": "GND"}, sch=(150 + i * 8, 106, 0), pcb=(78.0, FB_ROWS[sig], 0), lcsc="C53172")
JST_FP = "Connector_JST:JST_PH_B2B-PH-K_1x02_P2.00mm_Vertical"
add("J5", "Connector_Generic:Conn_01x02", "Speaker L (JST-PH)", JST_FP,
    {"1": "SPKF_LP", "2": "SPKF_LN"}, sch=(190, 96, 0), pcb=(85.0, U3Y - 4.0, 0), mpn="B2B-PH-K-S(LF)(SN)", lcsc=PH2_LCSC)
add("J6", "Connector_Generic:Conn_01x02", "Speaker R (JST-PH)", JST_FP,
    {"1": "SPKF_RP", "2": "SPKF_RN"}, sch=(190, 106, 0), pcb=(85.0, U3Y + 4.0, 0), mpn="B2B-PH-K-S(LF)(SN)", lcsc=PH2_LCSC)

# --- Headphone jack on the top edge, plug detect mutes the speaker amp ----------------------
# Tip/ring from U2.  TN is shorted to T while nothing is plugged in, so HP_DET sits at ~0 V
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    {"1": "SW_HI", "2": "BOOST_EN"}, sch=(16, 160, 0), pcb=(5.5, 40.0, 90), mpn=XH2_MPN, lcsc=XH2_LCSC)   # left edge, mid-height, like the panel switch
add("JP2", "Jumper:SolderJumper_2_Open", "always on (bridges the power switch)",
    "Jumper:SolderJumper-2_P1.3mm_Open_RoundedPad1.0x1.5mm",
    {"1": "SW_HI", "2": "BOOST_EN"}, sch=(24, 164, 0), pcb=(17.0, 40.0, 90))   # beside J16, room for an iron and the label
add("R28", "Device:R", "10k", R_SMD, {"1": "VSYS", "2": "SW_HI"}, sch=(30, 164, 90), pcb=(124.0, 36.5, 0), lcsc="C17414")
add("R27", "Device:R", "100k", R_SMD, {"1": "BOOST_EN", "2": "GND"}, sch=(36, 164, 90), pcb=(124.0, 39.0, 0), lcsc="C149504")
# Boost: TPS61023, 1 uH, 10 uF in, 2 x 22 uF + C1 out, 750k/100k -> 5.1 V (VREF 0.6 V).  About
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# Seed's pad rows, via up next to each input cap.
_R = U3X + 1.49   # MAX98306 right-side pad column; pins 14..8 top->bottom at 0.4 mm pitch
PREROUTES = [
    # AUDIO_L threads between the Seed's pad rows (y 46.82 sits between pins 23 and 22) and
    # comes up to C16; AUDIO_R loops under the Seed's lower edge to C17.  No crossings.
    ("AUDIO_L", "F.Cu", [("U1", "18"), (31.5, 46.82), (47.5, 46.82), (47.5, "C16:1"), ("C16", "1")]),
    ("AUDIO_R", "F.Cu", [("U1", "19"), (28.0, None), (28.0, 52.5), (51.0, 52.5), (51.0, "C17:1"), ("C17", "1")]),
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
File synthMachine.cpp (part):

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
// `make HP_DET=adc` builds with SYNTH_HP_DET_ADC (carrier only): the plug
// detect is read through the ADC on A5 instead of D13, which needs a wire from
// EXP pin 8 (HP_DET) to EXP pin 4 (A5). On the v0.3 carrier HP_DET can't
// reach a digital high: Q1's base-emitter junction, fed through R5, clamps it
// at about 0.8 V with a plug in (0 V without), so D13 reads low either way
// and the headphone amp would never be unmuted. See hardware/NEXT_REVISION.md.
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static constexpr Pin ROW_PINS[3] = {seed::D1, seed::D2, seed::D3};
static constexpr Pin C4_PIN = seed::D10;

// Speaker amp mute. Same pin on the prototype and the v0.3 carrier, different
// drive (see SpeakerAmp); the v0.4 carrier moved it to D0 to free I2C1.
#if defined(SYNTH_HW_CARRIER_V4)
static constexpr Pin SPEAKER_MUTE_PIN = seed::D0;
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static constexpr Pin SPEAKER_MUTE_PIN = seed::D11;
#endif
#if defined(SYNTH_HW_CARRIER)
static constexpr Pin HP_DET_PIN = seed::D13;  // jack switch: high = plug in
static constexpr Pin HP_MUTE_PIN = seed::D14; // TPA6138A2 ~MUTE, active low
#endif

// ADC channels: A0..A4 are the pots; with HP_DET=adc, channel 5 is A5.
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    pin.Init(SPEAKER_MUTE_PIN, GPIO::Mode::OUTPUT, GPIO::Pull::NOPULL);
    Mute();
  }
  void Mute() { pin.Write(true); }
  void Run() { pin.Write(false); }
#elif defined(SYNTH_HW_CARRIER)
  // Carrier: D11 (net MUTE) feeds the base of Q1 through 10k, and Q1's
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    pin.Init(SPEAKER_MUTE_PIN, GPIO::Mode::OUTPUT_OD, GPIO::Pull::NOPULL);
    Mute();
  }
  void Mute() { pin.Write(false); }
  void Run() { pin.Write(true); }
#endif
};
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// remember whether a plug is in.
class HeadphoneJack {
#if defined(SYNTH_HW_CARRIER)
  GPIO hpMute; // D14: TPA6138A2 ~MUTE, low = headphone amp muted
#if defined(SYNTH_HP_DET_ADC)
  DaisySeed *seed = nullptr; // HP_DET arrives on A5, see SYNTH_HP_DET_ADC
#else
  GPIO detect; // D13: HP_DET, high = plug inserted
#endif
  int level = 0;
  bool pluggedIn = false;
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    // ties HP_DET to the headphone amp's left output, and audio peaks on
    // that node would turn Q1 on and gate the speaker amp. A muted headphone
    // amp holds the node near ground.
    hpMute.Init(HP_MUTE_PIN, GPIO::Mode::OUTPUT, GPIO::Pull::NOPULL);
    hpMute.Write(false);
#if defined(SYNTH_HP_DET_ADC)
    seed = &hw;
#else
    (void)hw;
    detect.Init(HP_DET_PIN, GPIO::Mode::INPUT, GPIO::Pull::NOPULL);
#endif
  }

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
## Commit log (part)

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2025-08-25 Trying to get external usb midi working
